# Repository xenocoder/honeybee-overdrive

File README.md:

BJF effects Honey Bee Overdrive. Used the Madbean Yellow Shark schematic.

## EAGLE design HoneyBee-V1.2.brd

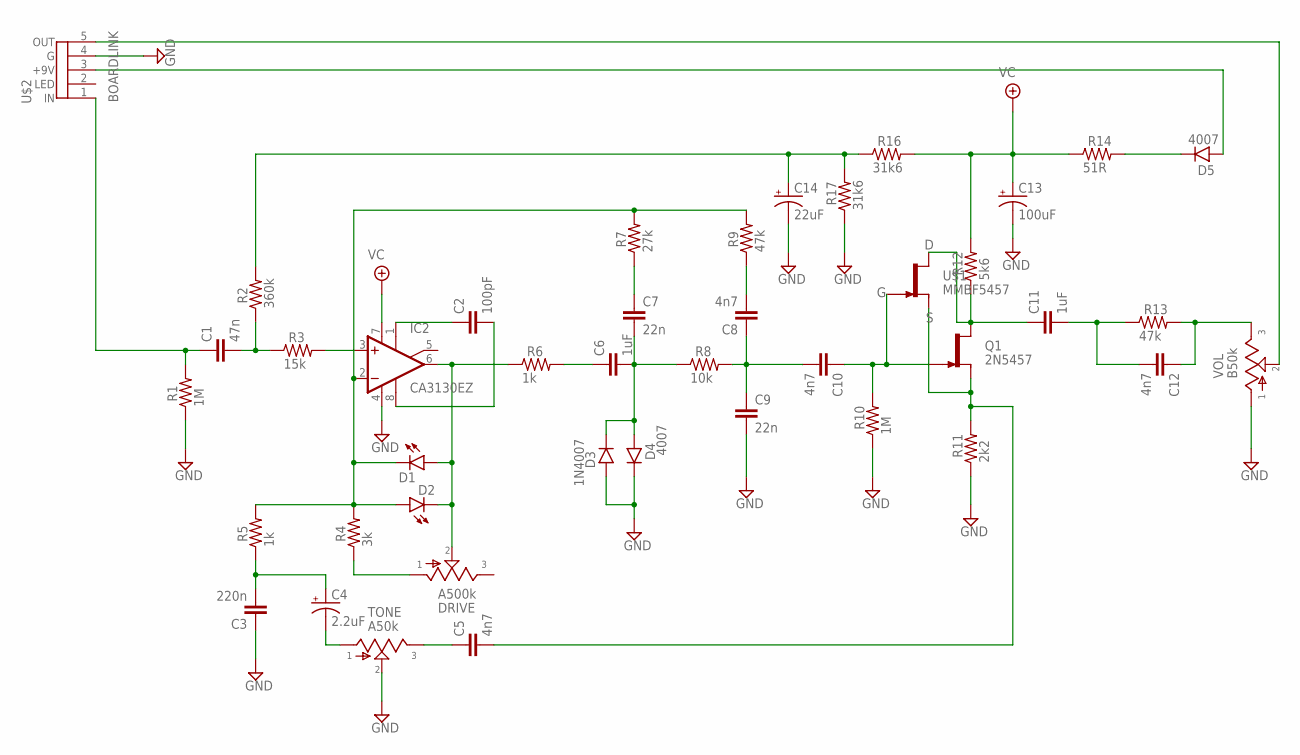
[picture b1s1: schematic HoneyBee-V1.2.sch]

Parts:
C1: 47n; 075X040
C2: 100pF; 050X030_025
C3: 220n; 080X050
C4: 2.2uF; 050_020_1
C5, C8, C10, C12: 4n7; 070X030
C6, C11: 1uF; 080X050
C7, C9: 22n; 075X030
C13: 100uF; 080_035_1
C14: 22uF; 050_020_1
D1, D2: LED3MM
D3: 1N4007; DO41-3
D4, D5: 4007; DO41-3
DRIVE: A500k; 16MM
IC2: CA3130EZ; DIL08
Q1: 2N5457; TO92-
R1, R10: 1M; R0207/3
R2: 360k; R0207/3
R3: 15k; R0207/3
R4: 3k; R0207/3
R5, R6: 1k; R0207/3
R7: 27k; R0207/3
R8: 10k; R0207/3
R9, R13: 47k; R0207/3
R11: 2k2; R0207/3
R12: 5k6; R0207/3
R14: 51R; R0207/3
R16, R17: 31k6; R0207/3
TONE: A50k; 16MM
U$1: MMBF5457; SOT23
U$2: BOARDLINK
VOL: B50k; 16MM

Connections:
GND: C3.1, C9.2, C13.-, C14.-, D3.A, D4.C, IC2.4 (V-), R1.1, R10.1, R11.1, R17.1, TONE.2, U$2.4 (G), VOL.1
unnamed: C1.2, R2.1, R3.1
unnamed: IC2.3 (+IN), R3.2
unnamed: C3.2, C4.+, R5.1
unnamed: D1.K (C), D2.A, IC2.2 (-IN), R4.2, R5.2, R7.2, R9.2
unnamed: C4.-, TONE.1
unnamed: C5.1, TONE.3
unnamed: C6.1, R6.2
unnamed: D1.A, D2.K (C), DRIVE.2, IC2.6 (OUT), R6.1
unnamed: DRIVE.1, R4.1
unnamed: C2.1, IC2.1 (ON1)
unnamed: C2.2, IC2.8 (OPT)
unnamed: C6.2, C7.2, D3.C, D4.A, R8.1
unnamed: C7.1, R7.1
unnamed: C8.1, C9.1, C10.2, R8.2
unnamed: C8.2, R9.1
unnamed: C10.1, Q1.1 (G), R10.2, U$1.3 (G)
unnamed: C5.2, Q1.2 (S), R11.2, U$1.2 (S)
unnamed: C11.1, Q1.3 (D), R12.1, U$1.1 (D)
unnamed: C14.+, R2.2, R16.1, R17.2
unnamed: C1.1, R1.2, U$2.1 (IN)
unnamed: C11.2, C12.2, R13.1
unnamed: C12.1, R13.2, VOL.3
unnamed: D5.C, R14.2
unnamed: D5.A, U$2.3 (+9V)
unnamed: U$2.5 (OUT), VOL.2
VC: C13.+, IC2.7 (V+), R12.2, R14.1, R16.2

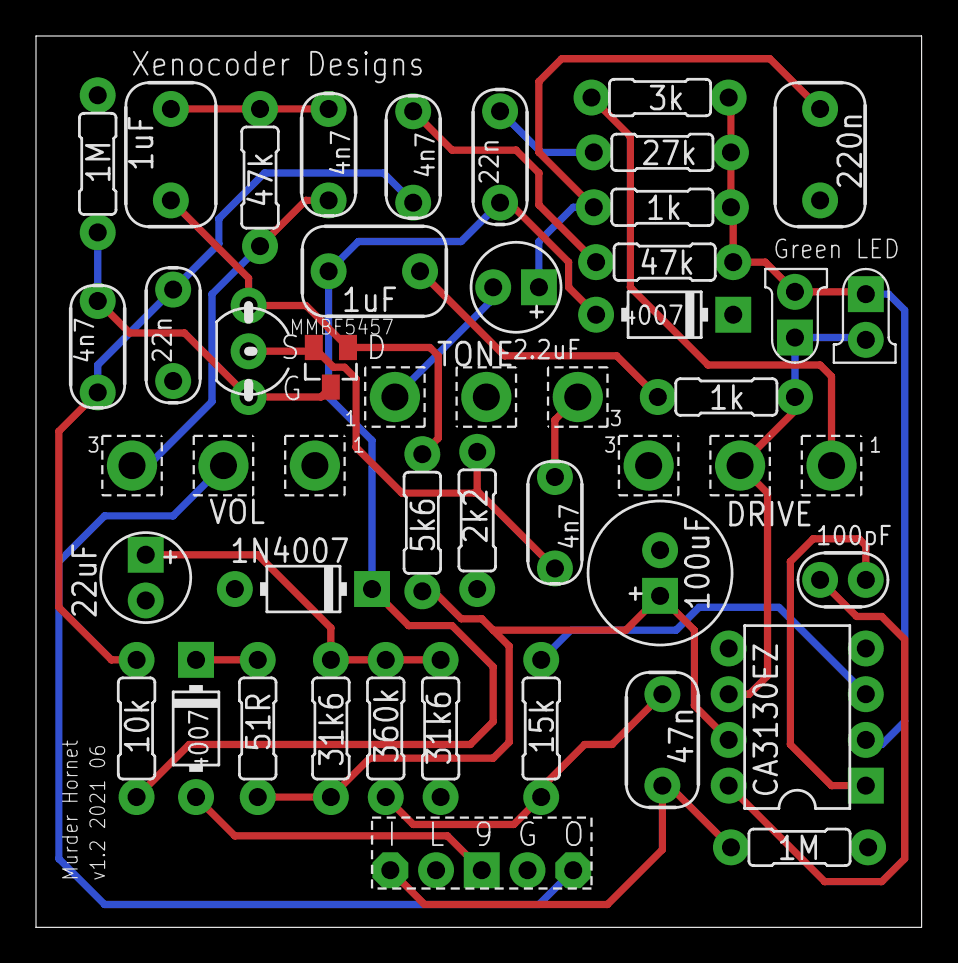
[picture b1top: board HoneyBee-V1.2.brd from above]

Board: 2 copper layers, 49.2 x 49.5 mm, 42 parts (0 on the bottom side), 27 nets.

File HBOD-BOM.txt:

Partlist

Exported from HoneyBee-V1.1.sch at 9/5/18 7:39 PM

EAGLE Version 9.1.0 Copyright (c) 1988-2018 Autodesk, Inc.

Assembly variant: 

Part     Value          Device       Package     Library          Sheet

+9V      +9V(T)         +9V(T)       SQUARE      mb_supply        1
C1       47n            075X0402     075X040     mb_caps-chicklet 1
C2       100pF          050X030_0251 050X030_025 mb_caps-ceramic  1
C3       220n           080X0502     080X050     mb_caps-chicklet 1
C4       2.2uF          0501         050_020_1   mb_caps-electro  1
C5       4n7            070X0302     070X030     mb_caps-chicklet 1
C6       1uF            080X0502     080X050     mb_caps-chicklet 1
C7       22n            075X0302     075X030     mb_caps-chicklet 1
C8       4n7            070X0302     070X030     mb_caps-chicklet 1
C9       22n            075X0302     075X030     mb_caps-chicklet 1
C10      4n7            070X0302     070X030     mb_caps-chicklet 1
C11      1uF            080X0502     080X050     mb_caps-chicklet 1
C12      4n7            070X0302     070X030     mb_caps-chicklet 1
C13      100uF          0801         080_035_1   mb_caps-electro  1
C14      22uF           0501         050_020_1   mb_caps-electro  1
D1       LED3MM         LED3MM       LED3MM      mb_diodes        1
D2       LED3MM         LED3MM       LED3MM      mb_diodes        1
D3       1N4007         1N400X.3     DO41-3      mb_diodes        1
D4       1N4007         1N400X.3     DO41-3      mb_diodes        1
D5       1N4007         1N400X.3     DO41-3      mb_diodes        1
D6       5v1 Zener      1N9ZENER     DO35-3      mb_diodes        1
DRIVE    A500k          POT16MM      16MM        mb_pots          1
G1       GND(T)         GND(T)       SQUARE      mb_supply        1
IC2      CA3130EZLMP    CA3130EZLMP  DIL08       mb_ics           1
IN       IN(T)          IN(T)        SQUARE      mb_supply        1
L                       PAD          SQUARE      mb_supply        1
LED      3mm            LED3MM       LED3MM      mb_diodes        1
NAT      A50k           POT16MM      16MM        mb_pots          1
OUT      OUT(T)         OUT(T)       SQUARE      mb_supply        1
Q1       2N5457         2N5457       TO92-       mb_trans         1
R1       1M             6MM.3        R0207/3     mb_resistors     1
R2       360k           6MM.3        R0207/3     mb_resistors     1
R3       15k            6MM.3        R0207/3     mb_resistors     1
R4       3k             6MM.3        R0207/3     mb_resistors     1
R5       1k             6MM.3        R0207/3     mb_resistors     1
R6       1k             6MM.3        R0207/3     mb_resistors     1
R7       27k            6MM.3        R0207/3     mb_resistors     1
R8       10k            6MM.3        R0207/3     mb_resistors     1
R9       47k            6MM.3        R0207/3     mb_resistors     1
R10      1M             6MM.3        R0207/3     mb_resistors     1
R11      2k2            6MM.3        R0207/3     mb_resistors     1
R12      5k6            6MM.3        R0207/3     mb_resistors     1
R13      47k            6MM.3        R0207/3     mb_resistors     1
R14      51R            6MM.3        R0207/3     mb_resistors     1
R15      1k             6MM.3        R0207/3     mb_resistors     1
R16      31k6           6MM.3        R0207/3     mb_resistors     1
R17      31k6           6MM.3        R0207/3     mb_resistors     1
VOL      B50k           POT16MM      16MM        mb_pots          1

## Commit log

2015-10-08 Initial upload
2015-10-08 Changes to layout and schematic.
2018-08-24 First board layout for Seeed Studio
2018-09-06 Added Updated Partslist
2018-10-19 Drill Guide
2021-10-18 Added SMD Fet layout
    Added FET pads to layout. This is version 1.2
